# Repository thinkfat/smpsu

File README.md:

# smpsu
Simple Switch Mode Power Supply with LM2676

KiCAD 5 Project

BOM:
 C1: 50V 68µF,  Panasonic 50SVPF68M

 C2, C3: 100nF 50V X7R 0805, Kemet C0805C104M5RACTU

 U1: LM2676SX-ADJ/NOPB
 
 R1, R2: 10k 1% 0805
 
 RV1: Trimpot 30k 25-turn, Bourns 3296W-1-303LF
 
 C4: 16V 1000µF, Panasonic 16SVPF1000M
 
 D1: 60V 5A Schottky, Diodes Inc. B560C-13-F
 
 L1: 22µH 3.5A, Murata #B966BS-220M=P3
 
 J1, J2: TE 282837-2

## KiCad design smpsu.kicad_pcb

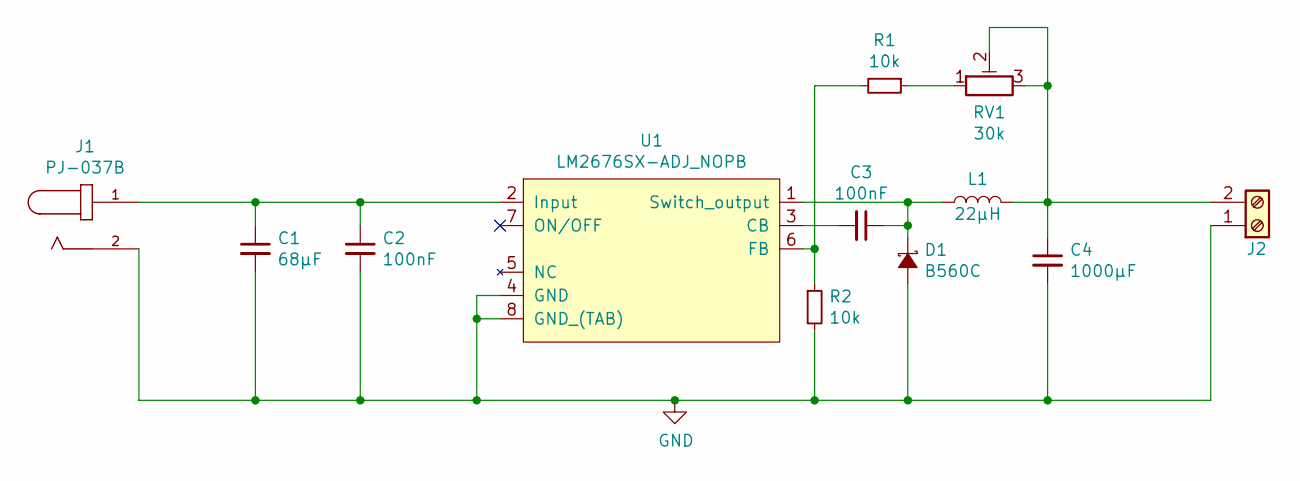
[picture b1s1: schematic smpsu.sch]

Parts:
C1: 68µF; CP_Elec_10x12.6
C2, C3: 100nF; C_0805_2012Metric_Pad1.15x1.40mm_HandSolder
C4: 1000µF; CP_Elec_10x12.6
D1: B560C; D_SMC
J1: PJ-037B; CUI_PJ-037B
J2: Screw_Terminal_01x02; TE_282837-2
L1: 22µH; L_10.4x10.4_H4.8
R1, R2: 10k; R_0805_2012Metric
RV1: 30k; Potentiometer_Vishay_T73XW_Horizontal
U1: LM2676SX-ADJ_NOPB; TO-263-7_TabPin8

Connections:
GND: C1.2, C2.2, C4.2, D1.2 (A), J1.2, J2.1, R2.2, U1.4 (GND), U1.8 (GND_(TAB))
unnamed: C1.1, C2.1, J1.1, U1.2 (Input)
unnamed: C3.1, D1.1 (K), L1.1, U1.1 (Switch_output)
unnamed: C3.2, U1.3 (CB)
unnamed: C4.1, J2.2, L1.2, RV1.2, RV1.3
unnamed: R1.1, RV1.1
unnamed: R1.2, R2.1, U1.6 (FB)

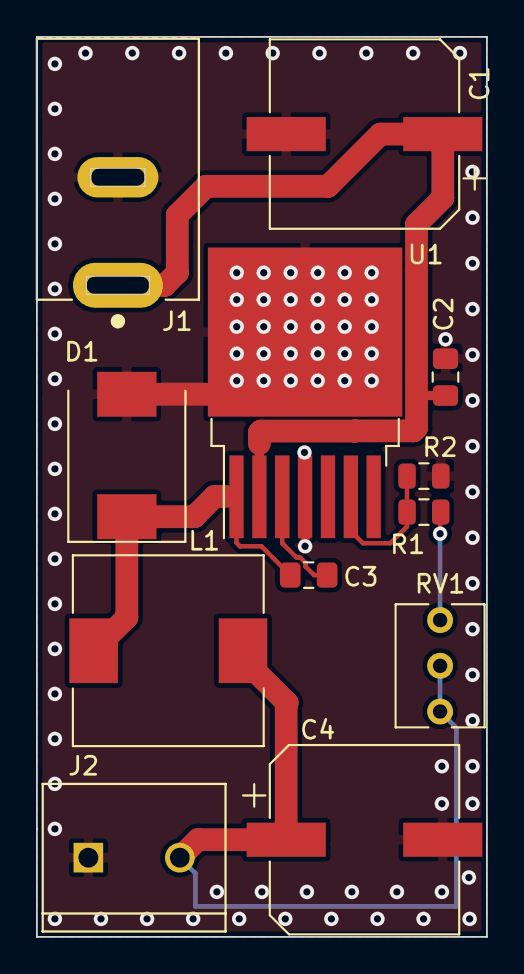
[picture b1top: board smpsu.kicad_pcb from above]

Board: 2 copper layers, 25.0 x 50.0 mm, 12 parts (0 on the bottom side), 7 nets.

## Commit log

2018-12-02 Switch Mode PSU Initial Commit
2018-12-21 WIP: redesign for better stability
